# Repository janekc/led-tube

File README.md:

# led-tube
PCB design for a portable, battery powered, tube shaped partylight.

It should run with 4 x 18650 lithium battery cells, that can be recharged through USB Power Delivery 3.0 with up to 18W. This would be achived using the IP5328P IC reference desing to handle charging and discharging of the 4 parallel cells.

The IP5328P can output uo to 5v 3.1A which, according to [Quins' real world LED Power consumption sheet](https://quinled.info/2020/03/12/digital-led-power-usage/), would be enough to power around 70 WS2812b 5050 RGB LEDs.

#### Extra Parts that you will need to buy if you want to build your own tube

- [Acrylic PLEXIGLASS Tubes 50/44mm](https://hbholzmaus.de/epages/Store7_Shop34800.sf/de_DE/?ObjectPath=/Shops/Shop34800/Categories/Rohre/%22Rohre%20satiniert%22)

- [QuinLED-ESP32-ABE Ethernet ESP32 Board](https://quinled.info/quinled-esp32/)

- [18650 lithium batteries](https://www.akkushop.de/de/3400mah-panasonic-18650-li-ion-akku-mit-eigener-schutzschaltung-ca.-69-x-1861mm-beachten/)

#### Projects that have been used as Inspiration

- https://github.com/YC-Lammy/IP5328P-powerbank_design

- https://hackaday.io/project/177748-modular-18650-power-bank

- https://www.flux.ai/jecstronic/powerbank-board

- https://github.com/janekc/diodeplate

- https://github.com/mstuij/QuinLED-ESP32-Breakout

- https://quinled.info/quinled-esp32-kicad-files/

#### Useful datasheets

- http://www.injoinic.com/wwwroot/uploads/files/20200221/ec29931791194a51119ee1d6a4a21efb.pdf

#### Links (not related directly)

- https://github.com/kkr0kk/PowerBank-DIY

- https://kicadrookie.blogspot.com/2022/07/kicad-projects-powerbank-pcb-IP5328P%20.html

- https://www.lcsc.com/search?q=IP5328P

- https://www.reddit.com/r/batteries/comments/onzm58/how_to_get_12v_for_a_amplifier_with_a_ip5328p/

- https://www.ti.com/lit/ug/tiduey1a/tiduey1a.pdf?ts=1696105000442

- https://hackaday.io/project/184947-pi-cm4-carrier-io-board

- https://www.aliexpress.com/item/33057941535.html?aff_fcid=06bf9dcd74484ab2a2f4b222b06f5361-1696411999482-09499-_AgWfRQ&aff_fsk=_AgWfRQ&aff_platform=shareComponent-detail&aff_trace_key=06bf9dcd74484ab2a2f4b222b06f5361-1696411999482-09499-_AgWfRQ&afSmartRedirect=y

- https://mm.kno.wled.ge/WLEDSR/Digital-Microphone-Hookup/

- https://kno.wled.ge/advanced/audio-reactive/

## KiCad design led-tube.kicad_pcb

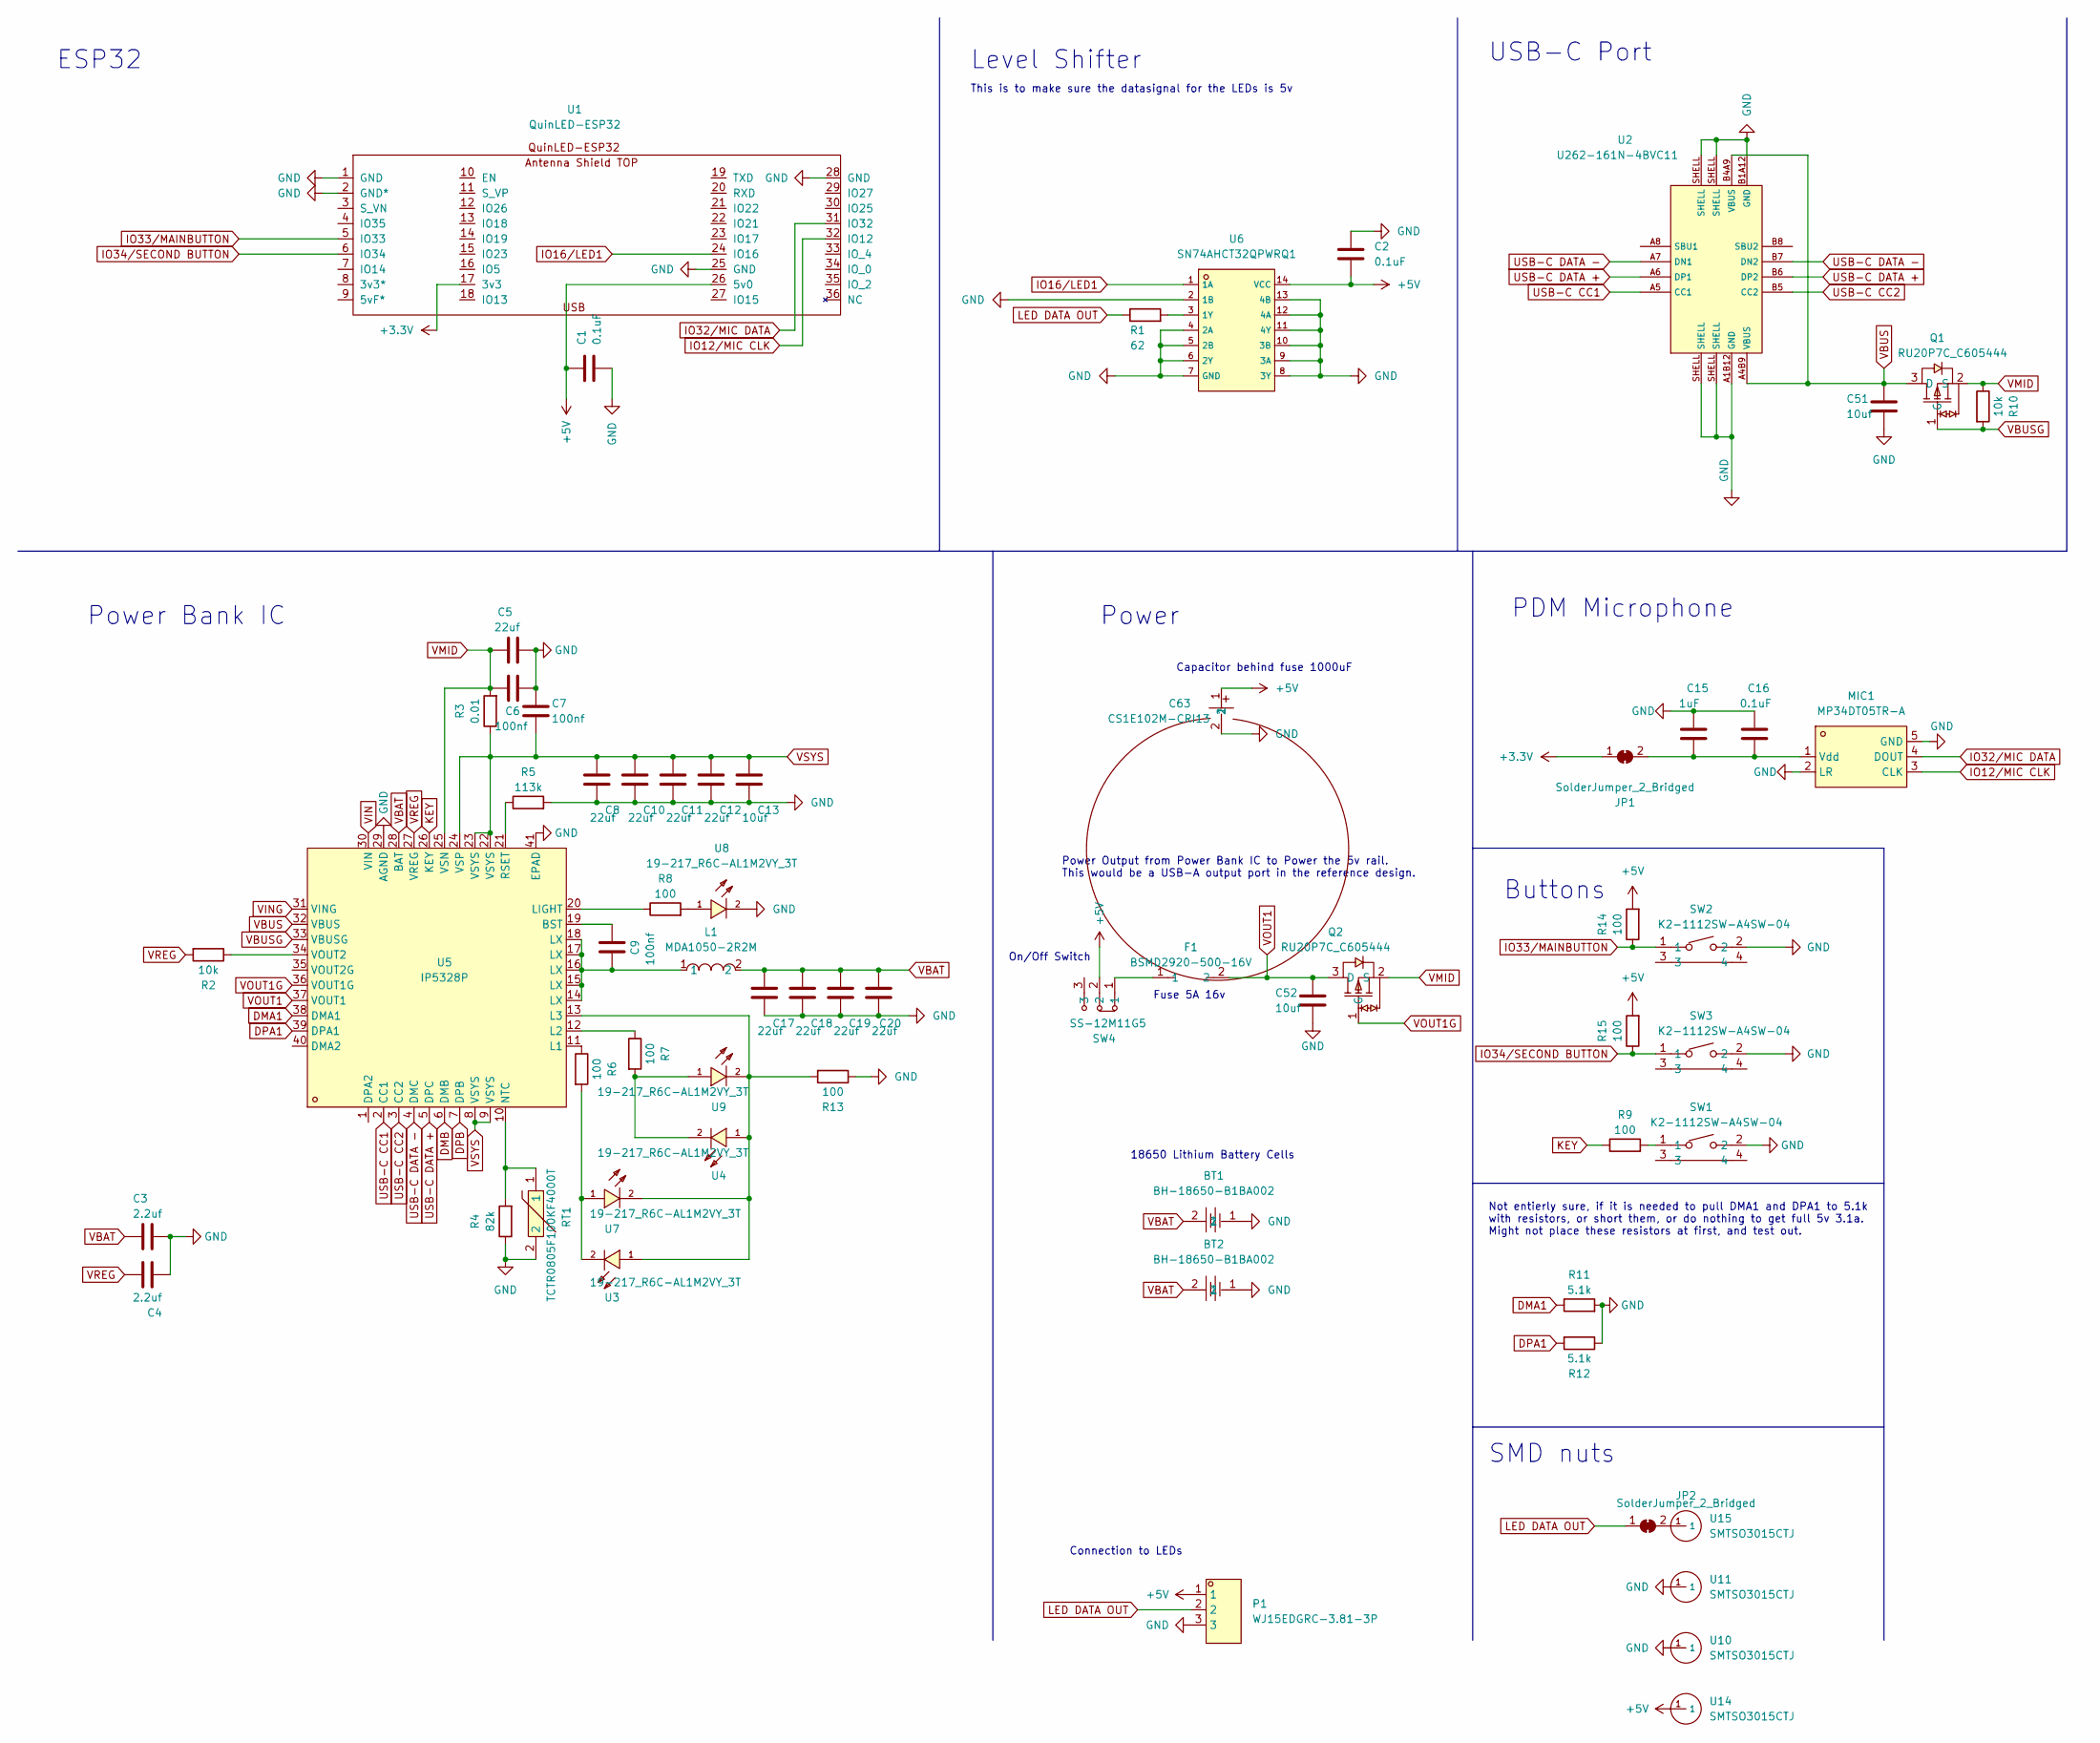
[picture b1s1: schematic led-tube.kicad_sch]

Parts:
BT1, BT2: BH-18650-B1BA002; BATTERY-SMD_18650-1S-L77.1-W20.7-1; LCSC Part C2988620
C1, C2, C16: 0.1uF; C_0603_1608Metric_Pad1.08x0.95mm_HandSolder
C3, C4: 2.2uf; C_0603_1608Metric_Pad1.08x0.95mm_HandSolder
C5, C8, C10, C11, C12, C17, C18, C19, C20: 22uf; C_0805_2012Metric_Pad1.18x1.45mm_HandSolder
C6, C7, C9: 100nf; C_0603_1608Metric_Pad1.08x0.95mm_HandSolder
C13, C51, C52: 10uf; C_0603_1608Metric_Pad1.08x0.95mm_HandSolder
C15: 1uF; C_0603_1608Metric_Pad1.08x0.95mm_HandSolder
C63: CS1E102M-CRI13; CAP-SMD_BD12.5-L13.0-W13.0-FD; LCSC Part C123705
F1: BSMD2920-500-16V; F2920; LCSC Part C910846
JP1, JP2: SolderJumper_2_Bridged; SolderJumper-2_P1.3mm_Bridged_RoundedPad1.0x1.5mm
L1: MDA1050-2R2M; IND-SMD_L11.0-W10.0; LCSC Part C2847559
MIC1: MP34DT05TR-A; MIC-SMD_5P-L3.0-W4.0-P0.85-BL; LCSC Part C2688664
P1: WJ15EDGRC-3.81-3P; CONN-TH_3P-P3.81_WJ15EDGRC-3.81-3P; LCSC Part C8406
Q1, Q2: RU20P7C_C605444; SOT-23-3_L2.9-W1.6-P1.90-LS2.8-BR; LCSC Part C605444
R1: 62; R_0603_1608Metric_Pad0.98x0.95mm_HandSolder
R2, R10: 10k; R_0603_1608Metric_Pad0.98x0.95mm_HandSolder
R3: 0.01; R_0603_1608Metric_Pad0.98x0.95mm_HandSolder
R4: 82k; R_0603_1608Metric_Pad0.98x0.95mm_HandSolder
R5: 113k; R_0603_1608Metric_Pad0.98x0.95mm_HandSolder
R6, R7, R8, R9, R13, R14, R15: 100; R_0603_1608Metric_Pad0.98x0.95mm_HandSolder
R11, R12: 5.1k; R_0603_1608Metric_Pad0.98x0.95mm_HandSolder
RT1: TCTR0805F100KF4000T; R0805; LCSC Part C525386
SW1, SW2, SW3: K2-1112SW-A4SW-04; KEY-TH_K2-1112SW-AXXW-XX; LCSC Part C223811
SW4: SS-12M11G5; SW-TH_XKB_SS-12M11XX; LCSC Part C2879839
U1: QuinLED-ESP32
U2: U262-161N-4BVC11; USB-3.1-SMD_U262-161N-4BVC11; LCSC # C319148
U3, U4, U7, U8, U9: 19-217_R6C-AL1M2VY_3T; LED0603-R-RD
U5: IP5328P; QFN-40_L6.0-W6.0-P0.50-BL-EP; LCSC Part C188809
U6: SN74AHCT32QPWRQ1; TSSOP-14_L5.0-W4.4-P0.65-LS6.5-BL; LCSC # C507218
U10, U11, U14, U15: SMTSO3015CTJ; SMTSO3030CTJ; LCSC # C2915308

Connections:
+3.3V: JP1.1 (A), U1.17 (3v3)
+5V: C1.1, C2.2, C63.1, P1.1, R14.2, R15.2, SW4.2, U1.26 (5v0), U6.14 (VCC), U14.1
DMA1: R11.1, U5.38 (DMA1)
DMB: U5.6 (DMB)
DPA1: R12.2, U5.39 (DPA1)
DPB: U5.7 (DPB)
GND: BT1.1, BT2.1, C1.2, C2.1, C3.1, C4.2, C5.2, C6.2, C7.1, C8.2, C10.2, C11.2, C12.2, C13.2, C15.1, C16.1, C17.2, C18.2, C19.2, C20.2, C51.2, C52.2, C63.2, MIC1.2 (LR), MIC1.5 (GND), P1.3, R4.1, R5.2, R11.2, R12.1, R13.1, RT1.2, SW1.2, SW2.2, SW3.2, U1.1 (GND), U1.2 (GND*), U1.25 (GND), U1.28 (GND), U2.A1B12 (GND), U2.B1A12 (GND), U2.SHELL, U5.29 (AGND), U5.41 (EPAD), U6.2 (1B), U6.4 (2A), U6.5 (2B), U6.6 (2Y), U6.7 (GND), U6.8 (3Y), U6.9 (3A), U6.10 (3B), U6.11 (4Y), U6.12 (4A), U6.13 (4B), U8.2 (C), U10.1, U11.1
IO12/MIC CLK: MIC1.3 (CLK), U1.32 (IO12)
IO16/LED1: U1.24 (IO16), U6.1 (1A)
IO32/MIC DATA: MIC1.4 (DOUT), U1.31 (IO32)
IO33/MAINBUTTON: R14.1, SW2.1, U1.5 (IO33)
IO34/SECOND BUTTON: R15.1, SW3.1, U1.6 (IO34)
KEY: R9.1, U5.26 (KEY)
LED DATA OUT: JP2.1 (A), P1.2, R1.1
unnamed: C9.1, L1.1, U5.14 (LX), U5.15 (LX), U5.16 (LX), U5.17 (LX), U5.18 (LX)
unnamed: F1.1, SW4.1
unnamed: C15.2, C16.2, JP1.2 (B), MIC1.1 (Vdd)
unnamed: JP2.2 (B), U15.1
unnamed: R9.2, SW1.1
unnamed: R13.2, U3.1 (A), U4.1 (A), U5.13 (L3), U7.2 (C), U9.2 (C)
unnamed: R6.2, U3.2 (C), U7.1 (A)
unnamed: R7.2, U4.2 (C), U9.1 (A)
unnamed: C9.2, U5.19 (BST)
unnamed: R6.1, U5.11 (L1)
unnamed: R7.1, U5.12 (L2)
unnamed: R8.1, U5.20 (LIGHT)
unnamed: R4.2, RT1.1, U5.10 (NTC)
unnamed: R5.1, U5.21 (RSET)
unnamed: R2.1, U5.34 (VOUT2)
unnamed: R1.2, U6.3 (1Y)
unnamed: R8.2, U8.1 (A)
USB-C CC1: U2.A5 (CC1), U5.2 (CC1)
USB-C CC2: U2.B5 (CC2), U5.3 (CC2)
USB-C DATA +: U2.A6 (DP1), U2.B6 (DP2), U5.5 (DPC)
USB-C DATA -: U2.A7 (DN1), U2.B7 (DN2), U5.4 (DMC)
VBAT: BT1.2, BT2.2, C3.2, C17.1, C18.1, C19.1, C20.1, L1.2, U5.28 (BAT)
VBUS: C51.1, Q1.3 (D), U2.A4B9 (VBUS), U2.B4A9 (VBUS), U5.32 (VBUS)
VBUSG: Q1.1 (G), R10.2, U5.33 (VBUSG)
VIN: U5.30 (VIN)
VING: U5.31 (VING)
VMID: C5.1, C6.1, Q1.2 (S), Q2.2 (S), R3.2, R10.1, U5.25 (VSN)
VOUT1: C52.1, F1.2, Q2.3 (D), U5.37 (VOUT1)
VOUT1G: Q2.1 (G), U5.36 (VOUT1G)
VREG: C4.1, R2.2, U5.27 (VREG)
VSYS: C7.2, C8.1, C10.1, C11.1, C12.1, C13.1, R3.1, U5.8 (VSYS), U5.9 (VSYS), U5.22 (VSYS), U5.23 (VSYS), U5.24 (VSP)

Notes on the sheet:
SMD nuts
18650 Lithium Battery Cells
Fuse 5A 16v
Capacitor behind fuse 1000uF
Power Bank IC
On/Off Switch
Power
PDM Microphone
USB-C Port
Buttons
Connection to LEDs
This is to make sure the datasignal for the LEDs is 5v
Level Shifter
Power Output from Power Bank IC to Power the 5v rail. This would be a USB-A output port in the reference design.
Not entierly sure, if it is needed to pull DMA1 and DPA1 to 5.1k with resistors, or short them, or do nothing to get full 5v 3.1a. Might not place these resistors at first, and test out.
ESP32

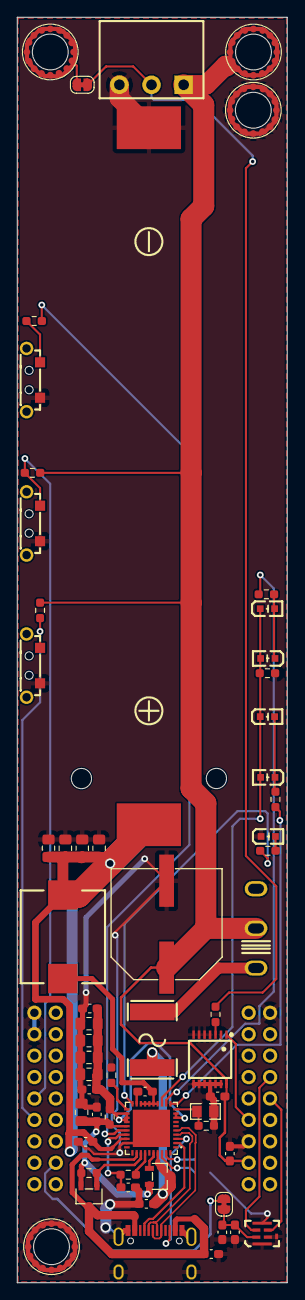
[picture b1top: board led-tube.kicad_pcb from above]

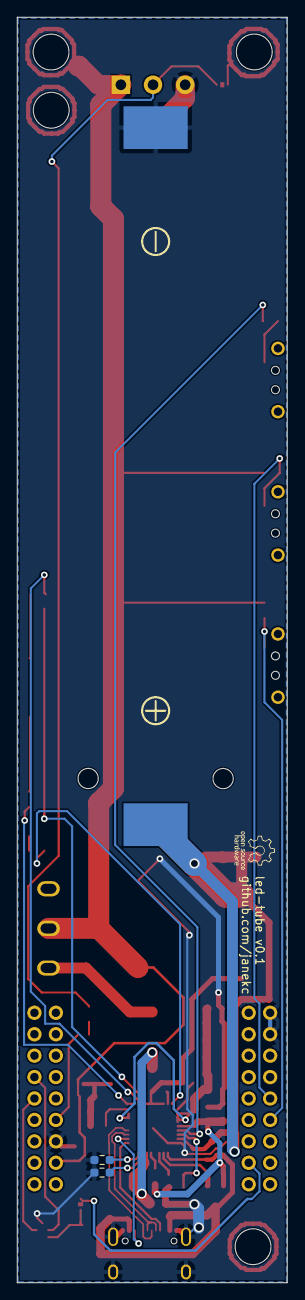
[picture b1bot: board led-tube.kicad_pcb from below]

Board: 2 copper layers, 32.0 x 150.0 mm, 65 parts (3 on the bottom side), 41 nets.

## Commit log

2023-10-02 add some links
2023-10-02 insert picture
2023-10-04 connect unconnected pieces, add micro usb for charging
2023-11-02 place components, don't place leds but use ledstrips instead
2023-11-02 add opensource hardware logo
2023-11-02 use CERN-OHL-P-2.0 license
2023-11-02 add gitignore
2023-11-02 generate gerber and drill files
2023-11-02 export more 3d models
